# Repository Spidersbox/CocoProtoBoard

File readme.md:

# CocoProtoBoard<br>
<br>
Forked from https://github.com/JayesonLS/TandyCircuitsAndLogic <br>
<br>
did some editing to get kicad DRC to pass clean.

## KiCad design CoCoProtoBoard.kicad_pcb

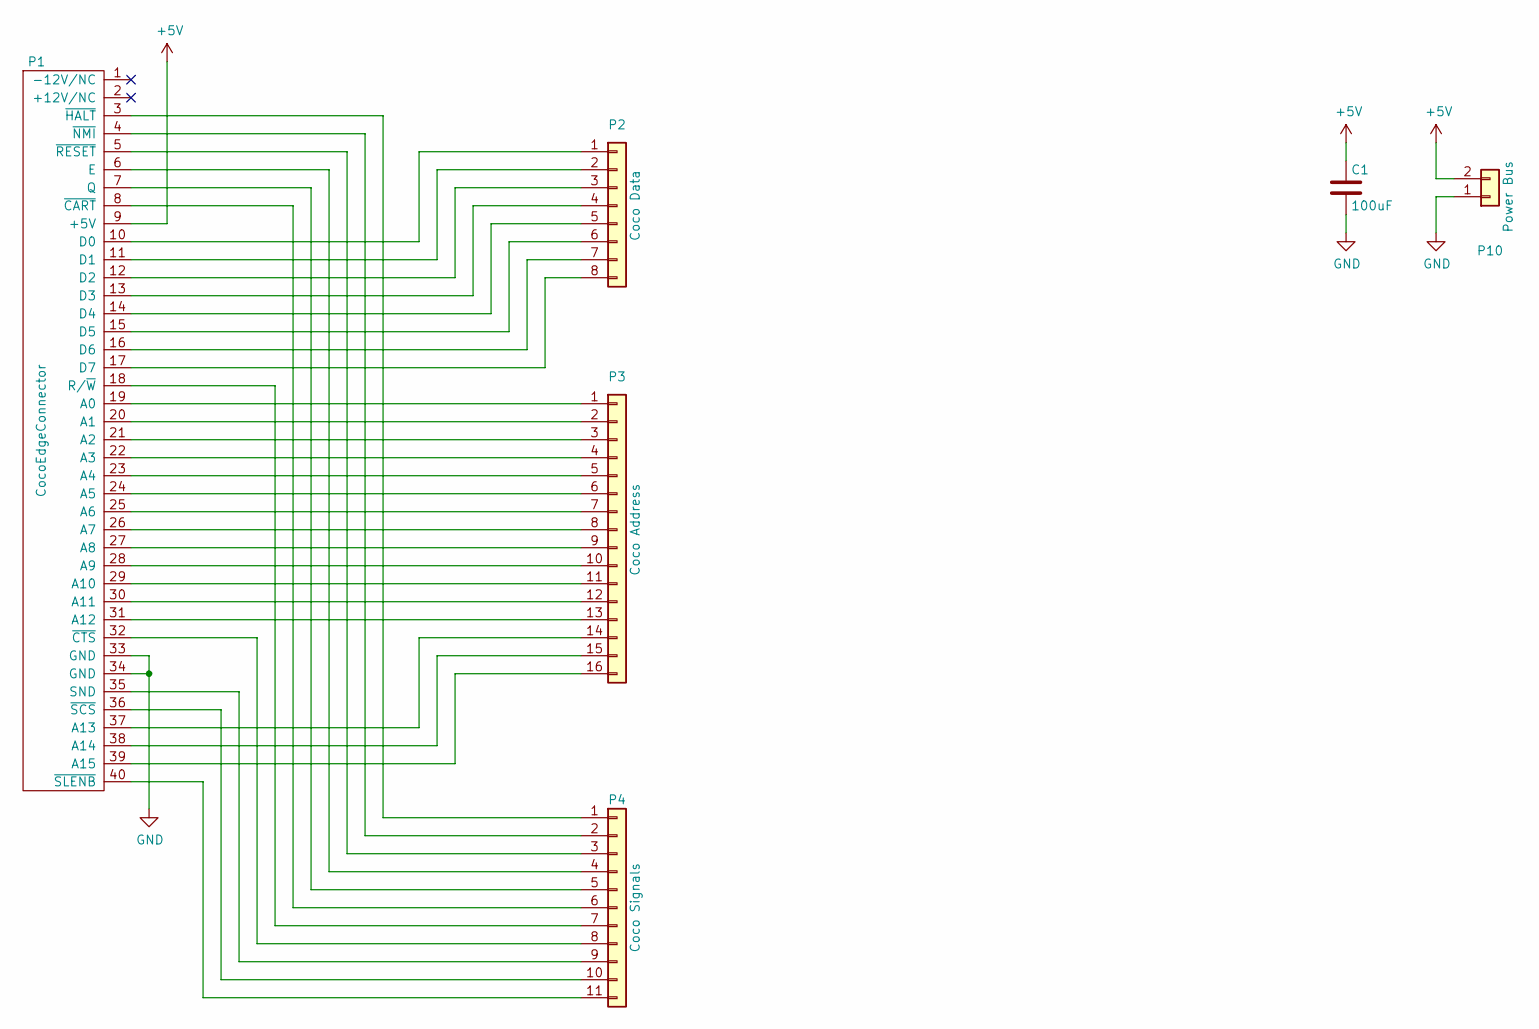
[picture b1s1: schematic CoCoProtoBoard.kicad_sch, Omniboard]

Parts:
C1: 100uF; C_Radial_D6.3mm_H7.0mm_P2.50mm
P1: CocoEdgeConnector; CocoCardEdge
P2: Coco Data; DIP-16_W7.62mm
P3: Coco Address; DIP-32_W15.24mm
P4: Coco Signals; DIP-22_W10.16mm
P10: Power Bus; DIP-61_W300mm

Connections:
+5V: C1.1, P1.9 (+5V), P10.2
GND: C1.2, P1.33 (GND), P1.34 (GND), P10.1
unnamed: P1.19 (A0), P3.1
unnamed: P1.20 (A1), P3.2
unnamed: P1.21 (A2), P3.3
unnamed: P1.22 (A3), P3.4
unnamed: P1.23 (A4), P3.5
unnamed: P1.24 (A5), P3.6
unnamed: P1.25 (A6), P3.7
unnamed: P1.26 (A7), P3.8
unnamed: P1.27 (A8), P3.9
unnamed: P1.28 (A9), P3.10
unnamed: P1.29 (A10), P3.11
unnamed: P1.30 (A11), P3.12
unnamed: P1.31 (A12), P3.13
unnamed: P1.37 (A13), P3.14
unnamed: P1.38 (A14), P3.15
unnamed: P1.39 (A15), P3.16
unnamed: P1.10 (D0), P2.1
unnamed: P1.11 (D1), P2.2
unnamed: P1.12 (D2), P2.3
unnamed: P1.13 (D3), P2.4
unnamed: P1.14 (D4), P2.5
unnamed: P1.15 (D5), P2.6
unnamed: P1.16 (D6), P2.7
unnamed: P1.17 (D7), P2.8
unnamed: P1.6 (E), P4.4
unnamed: P1.7 (Q), P4.5
unnamed: P1.18 (R/~W), P4.7
unnamed: P1.35 (SND), P4.9
unnamed: P1.8 (~CART), P4.6
unnamed: P1.32 (~CTS), P4.8
unnamed: P1.3 (~HALT), P4.1
unnamed: P1.4 (~NMI), P4.2
unnamed: P1.5 (~RESET), P4.3
unnamed: P1.36 (~SCS), P4.10
unnamed: P1.40 (~SLENB), P4.11

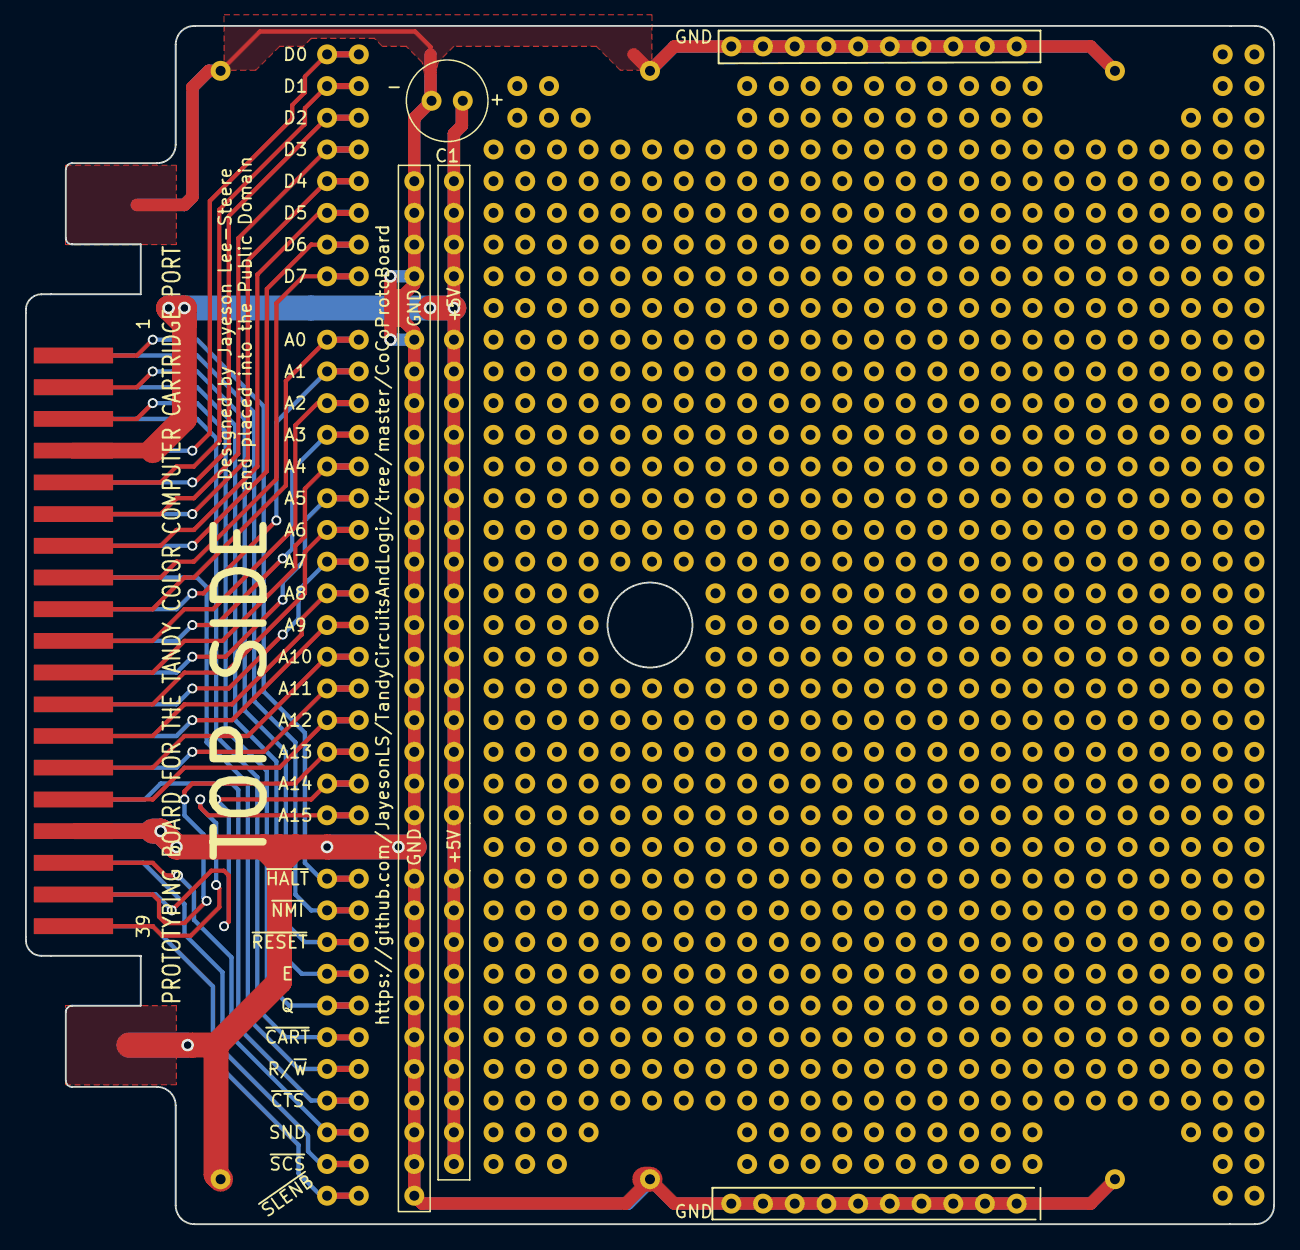
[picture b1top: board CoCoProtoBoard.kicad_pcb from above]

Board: 2 copper layers, 100.0 x 96.0 mm, 6 parts (0 on the bottom side), 37 nets.

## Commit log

2026-01-12 Initial push
2026-01-12 create gitignore
2026-01-12 removed backups
2026-01-12 created Gerbers
2026-01-20 a little cleanup and new Gerbers

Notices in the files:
CoCoProtoBoard.kicad_pcb:
and placed into the Public Domain
